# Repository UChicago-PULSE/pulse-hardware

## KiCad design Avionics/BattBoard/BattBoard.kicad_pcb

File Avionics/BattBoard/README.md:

Battery board schematic and board is found here.
Currently have uploaded both the schematic and PCB design

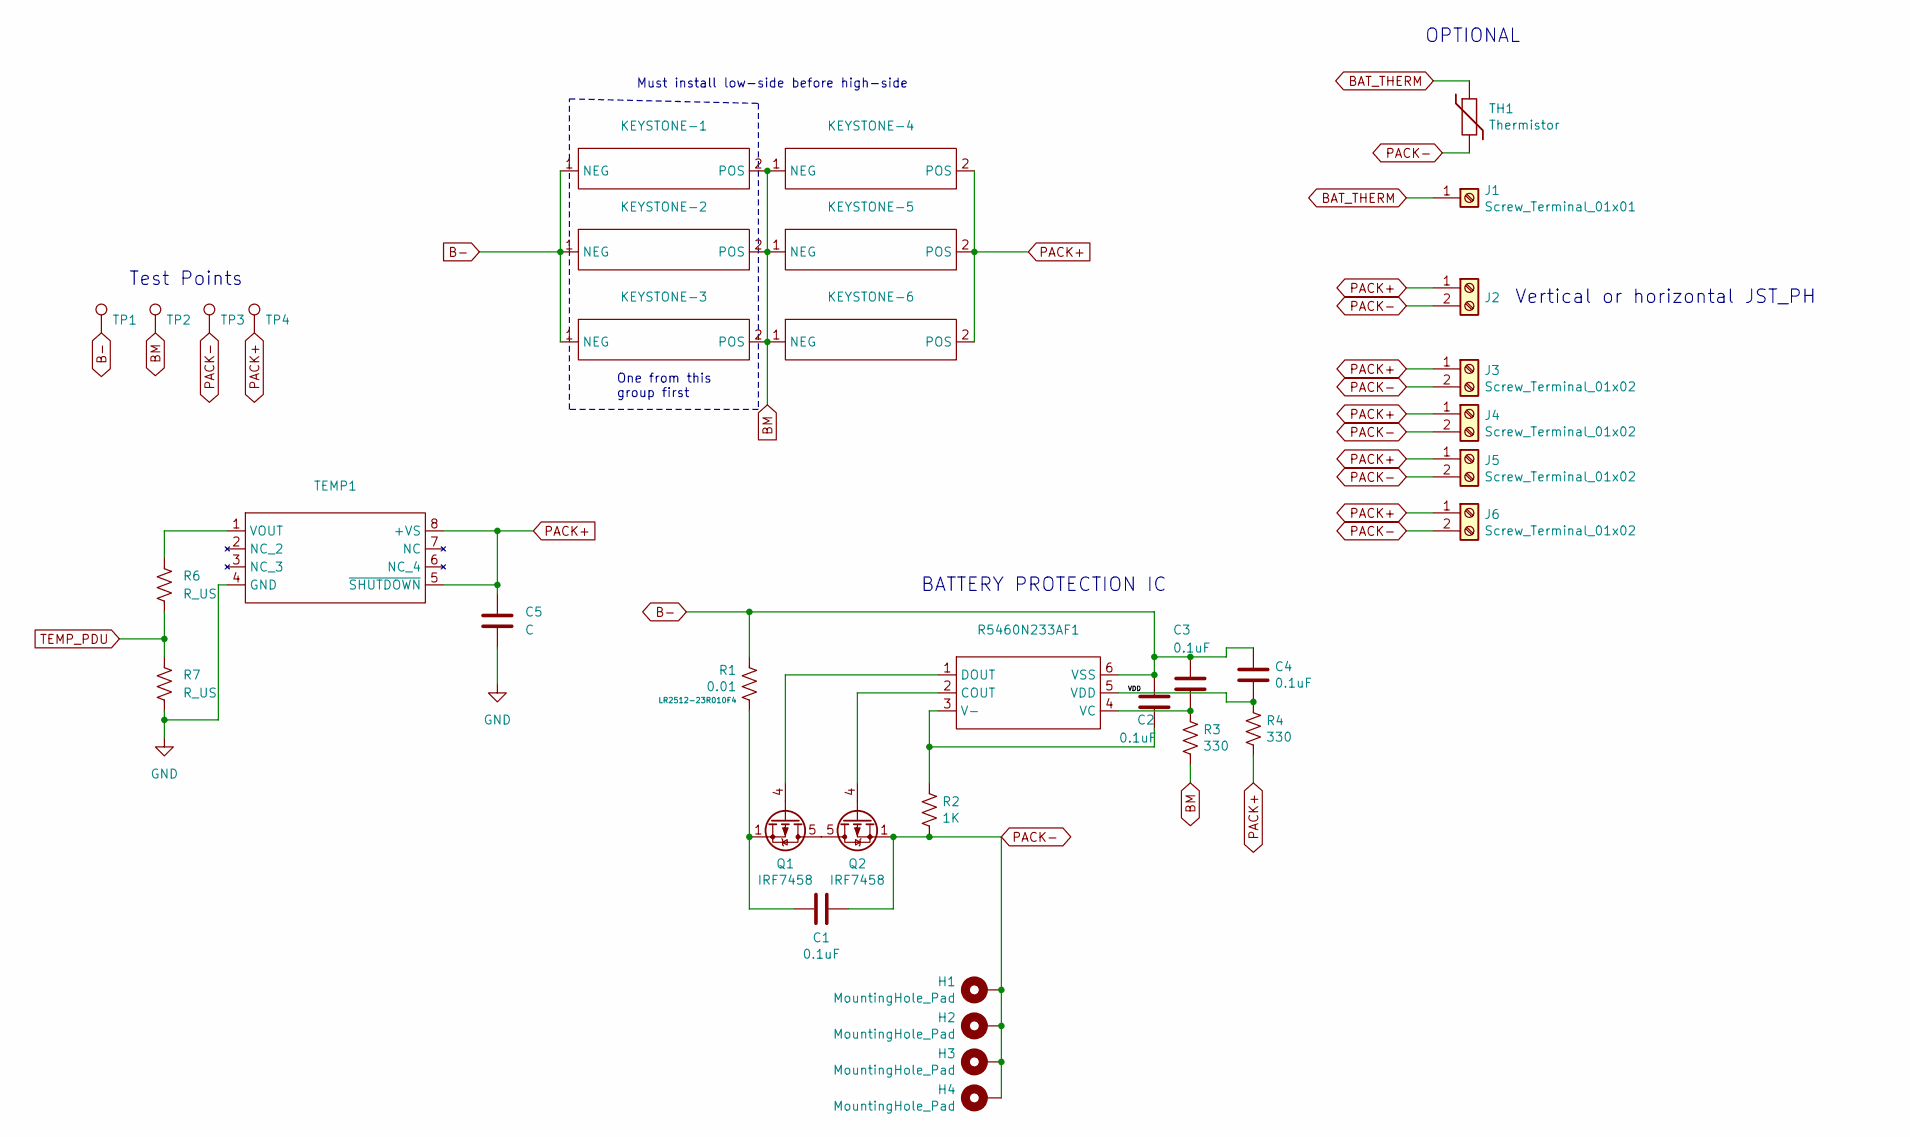
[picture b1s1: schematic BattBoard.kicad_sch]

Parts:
C1, C2, C3, C4: 0.1uF; C_0603_1608Metric
C5: C; C_0603_1608Metric
H1, H2, H3, H4: MountingHole_Pad; MountingHole_3.2mm_M3_DIN965_Pad
J1: Screw_Terminal_01x01; PinHeader_1x01_P1.00mm_Vertical
J2: JST_PH_S2B-PH-SM4; JST_PH_S2B-PH-SM4-TB_1x02-1MP_P2.00mm_Horizontal
J3, J4, J5, J6: Screw_Terminal_01x02; TerminalBlock_Altech_AK300-2_P5.00mm
KEYSTONE-1, KEYSTONE-2, KEYSTONE-3, KEYSTONE-4, KEYSTONE-5, KEYSTONE-6: BatteryHolder_Keystone_1042_1x18650
Q1, Q2: IRF7458; SOIC-8_3.9x4.9mm_P1.27mm
R1: 0.01; R_2512_6332Metric
R2: 1K; R_0603_1608Metric
R3, R4: 330; R_0603_1608Metric
R6, R7: R_US; R_0603_1608Metric
R5460N233AF1: PinHeader_2x03_P2.54mm_Vertical_SMD
TEMP1: Rohm_RPR-0521RS
TH1: Thermistor; R_Axial_DIN0204_L3.6mm_D1.6mm_P5.08mm_Vertical
TP1, TP2, TP3, TP4: TestPoint; TestPoint_Loop_D1.80mm_Drill1.0mm_Beaded

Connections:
/VDD: C4.2, R4.2, R5460N233AF1.5 (VDD)
B-: C2.1, C3.1, C4.1, KEYSTONE-1.1 (NEG), KEYSTONE-2.1 (NEG), KEYSTONE-3.1 (NEG), R1.1, R5460N233AF1.6 (VSS), TP1.1
BAT_THERM: J1.1, TH1.1
BM: KEYSTONE-1.2 (POS), KEYSTONE-2.2 (POS), KEYSTONE-3.2 (POS), KEYSTONE-4.1 (NEG), KEYSTONE-5.1 (NEG), KEYSTONE-6.1 (NEG), R3.1, TP2.1
GND: C5.2, R7.2, TEMP1.4 (GND)
unnamed: C1.1, Q1.1 (S), Q1.2 (S), Q1.3 (S), R1.2
unnamed: Q1.5 (D), Q1.6 (D), Q1.7 (D), Q1.8 (D), Q2.5 (D), Q2.6 (D), Q2.7 (D), Q2.8 (D)
unnamed: Q1.4 (G), R5460N233AF1.1 (DOUT)
unnamed: Q2.4 (G), R5460N233AF1.2 (COUT)
unnamed: C2.2, R2.1, R5460N233AF1.3 (V-)
unnamed: C3.2, R3.2, R5460N233AF1.4 (VC)
unnamed: R6.1, TEMP1.1 (VOUT)
PACK+: C5.1, J2.1, J3.1, J4.1, J5.1, J6.1, KEYSTONE-4.2 (POS), KEYSTONE-5.2 (POS), KEYSTONE-6.2 (POS), R4.1, TEMP1.5 (~SHUTDOWN), TEMP1.8 (+VS), TP4.1
PACK-: C1.2, H1.1, H2.1, H3.1, H4.1, J2.2, J3.2, J4.2, J5.2, J6.2, Q2.1 (S), Q2.2 (S), Q2.3 (S), R2.2, TH1.2, TP3.1
TEMP_PDU: R6.2, R7.1

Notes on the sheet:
Vertical or horizontal JST_PH
Test Points
OPTIONAL
One from this group first
Must install low-side before high-side
BATTERY PROTECTION IC

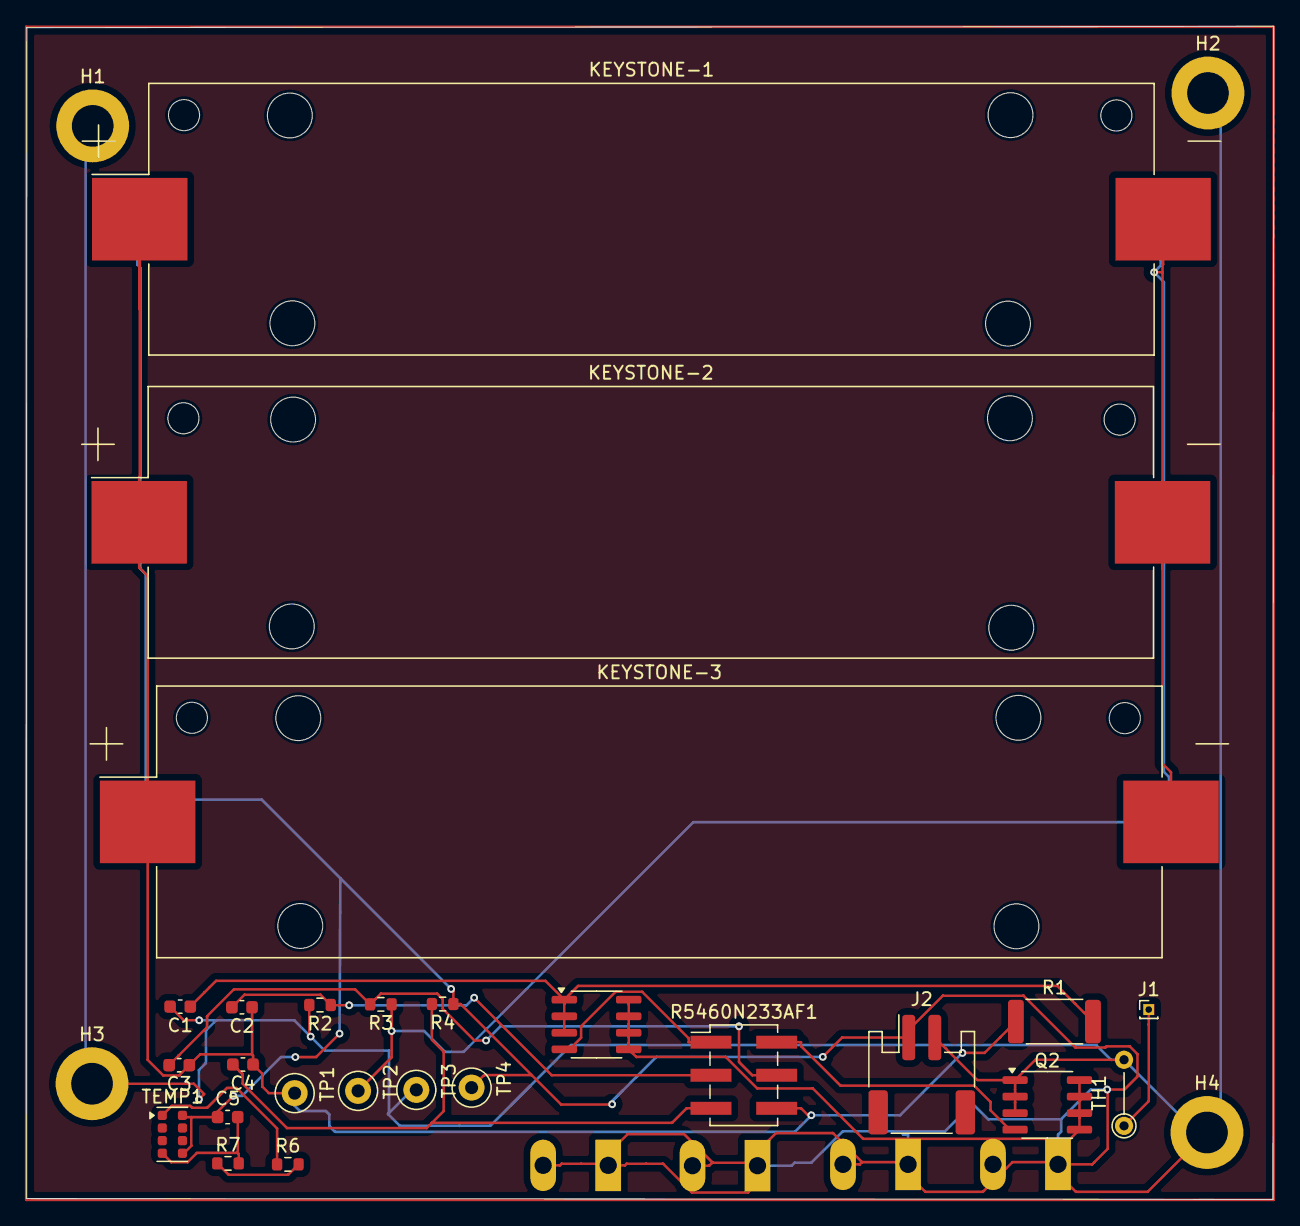
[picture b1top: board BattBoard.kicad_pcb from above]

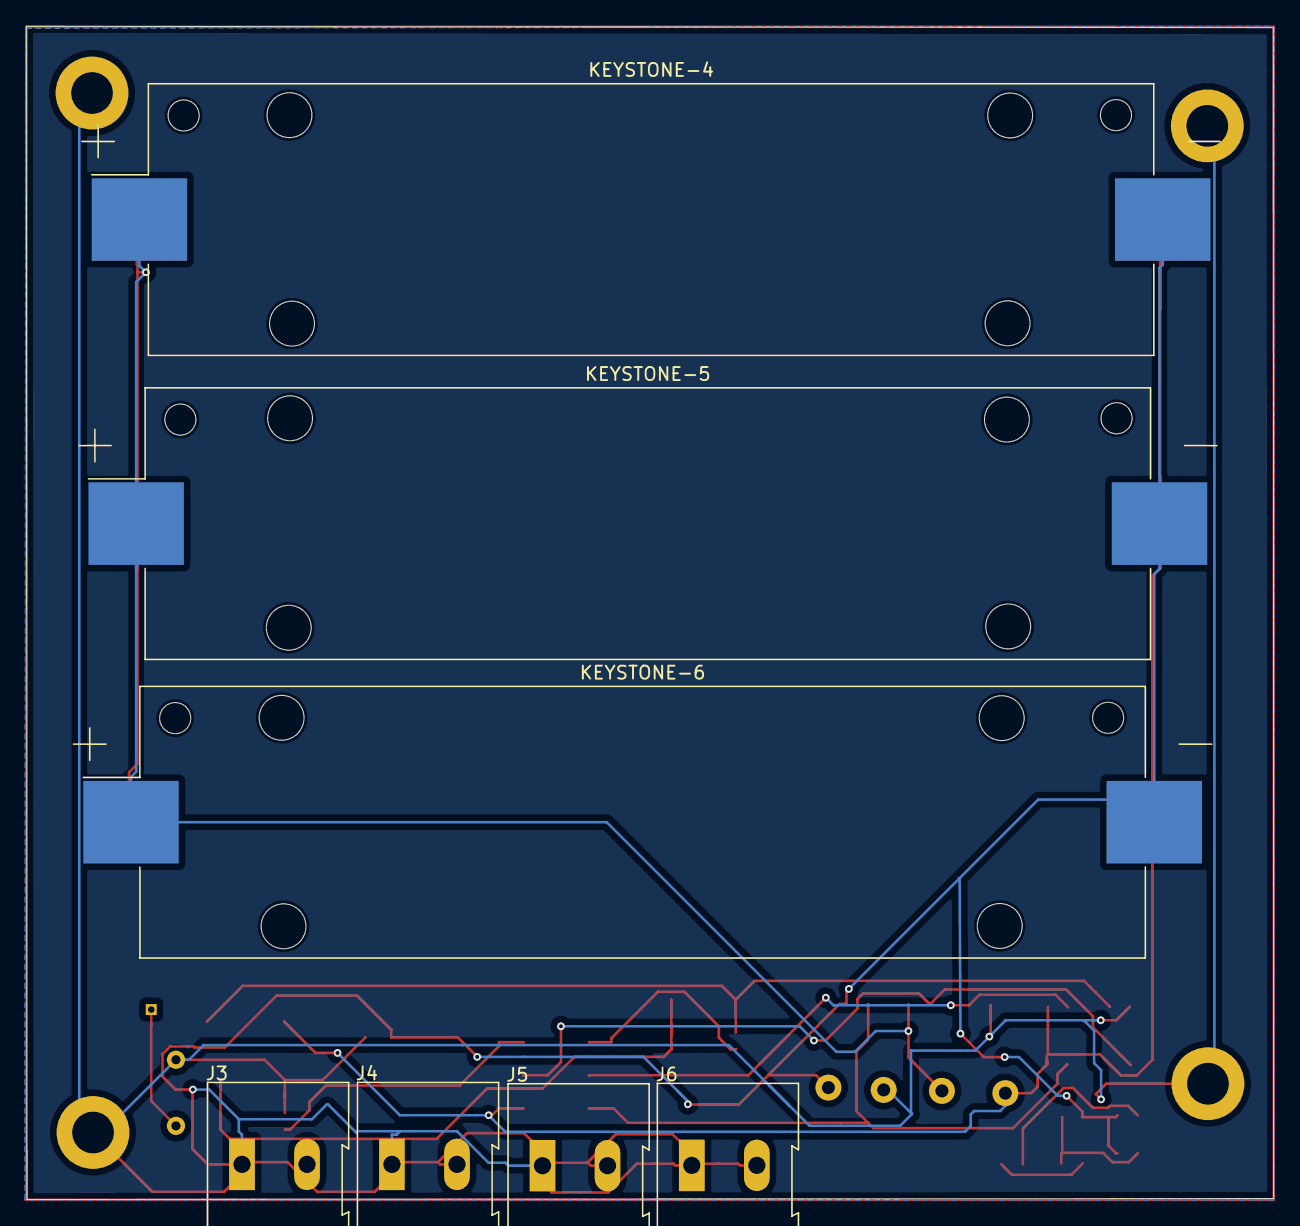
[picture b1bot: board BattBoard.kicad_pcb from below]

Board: 2 copper layers, 95.9 x 90.2 mm, 36 parts (7 on the bottom side), 15 nets.

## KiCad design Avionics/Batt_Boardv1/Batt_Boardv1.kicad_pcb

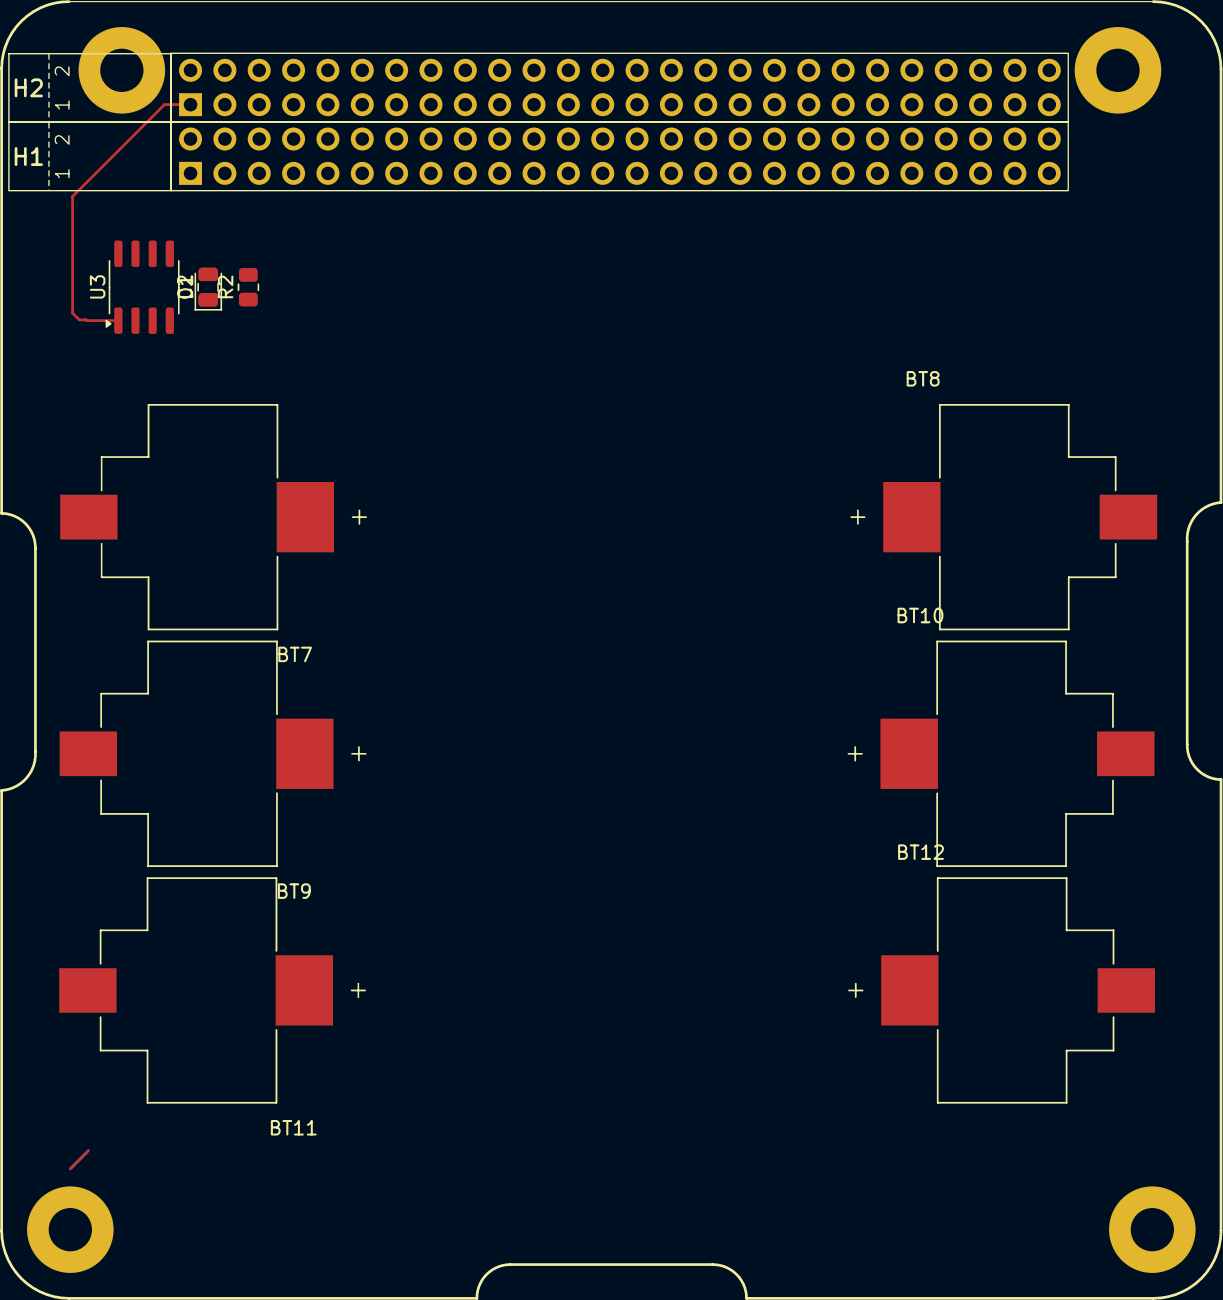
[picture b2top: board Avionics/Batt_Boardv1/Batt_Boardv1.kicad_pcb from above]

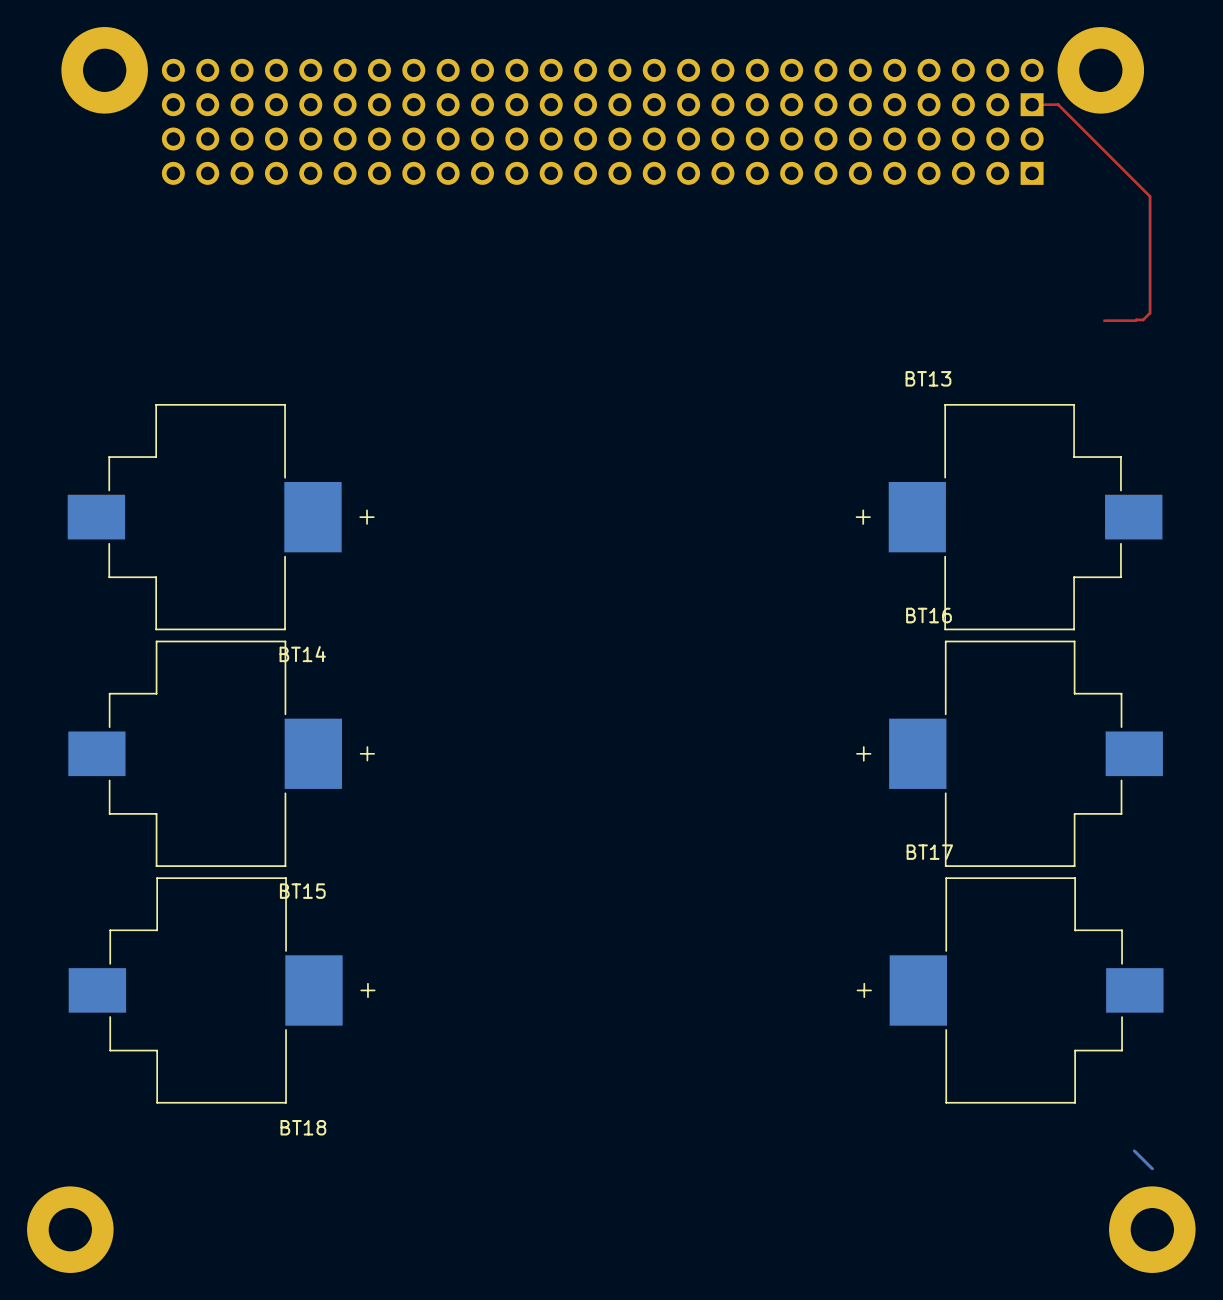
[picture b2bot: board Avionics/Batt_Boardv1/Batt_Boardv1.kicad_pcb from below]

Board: 2 copper layers, 17 parts (6 on the bottom side), 4 nets.

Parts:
BT7, BT8, BT9, BT10, BT11, BT12, BT13, BT14, BT15, BT16, BT17, BT18: 54; BAT_254TR
C2: 0.1µF; C_0805_2012Metric
D1: TEMP_PWR; LED_0805_2012Metric
R2: 15; R_0805_2012Metric
U1: PC104ConnectorFootprint (1)
U3: TMP36xS; SOIC-8_3.9x4.9mm_P1.27mm

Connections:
/batt_board_temp: U1.53 (TEMP_1), U3.1 (V_{OUT})
unnamed: C2.1, D1.2 (A), U3.5 (~SHUTDOWN), U3.8 (+Vs)
unnamed: D1.1 (K), R2.1
unnamed: C2.2, R2.2, U3.4 (GND)

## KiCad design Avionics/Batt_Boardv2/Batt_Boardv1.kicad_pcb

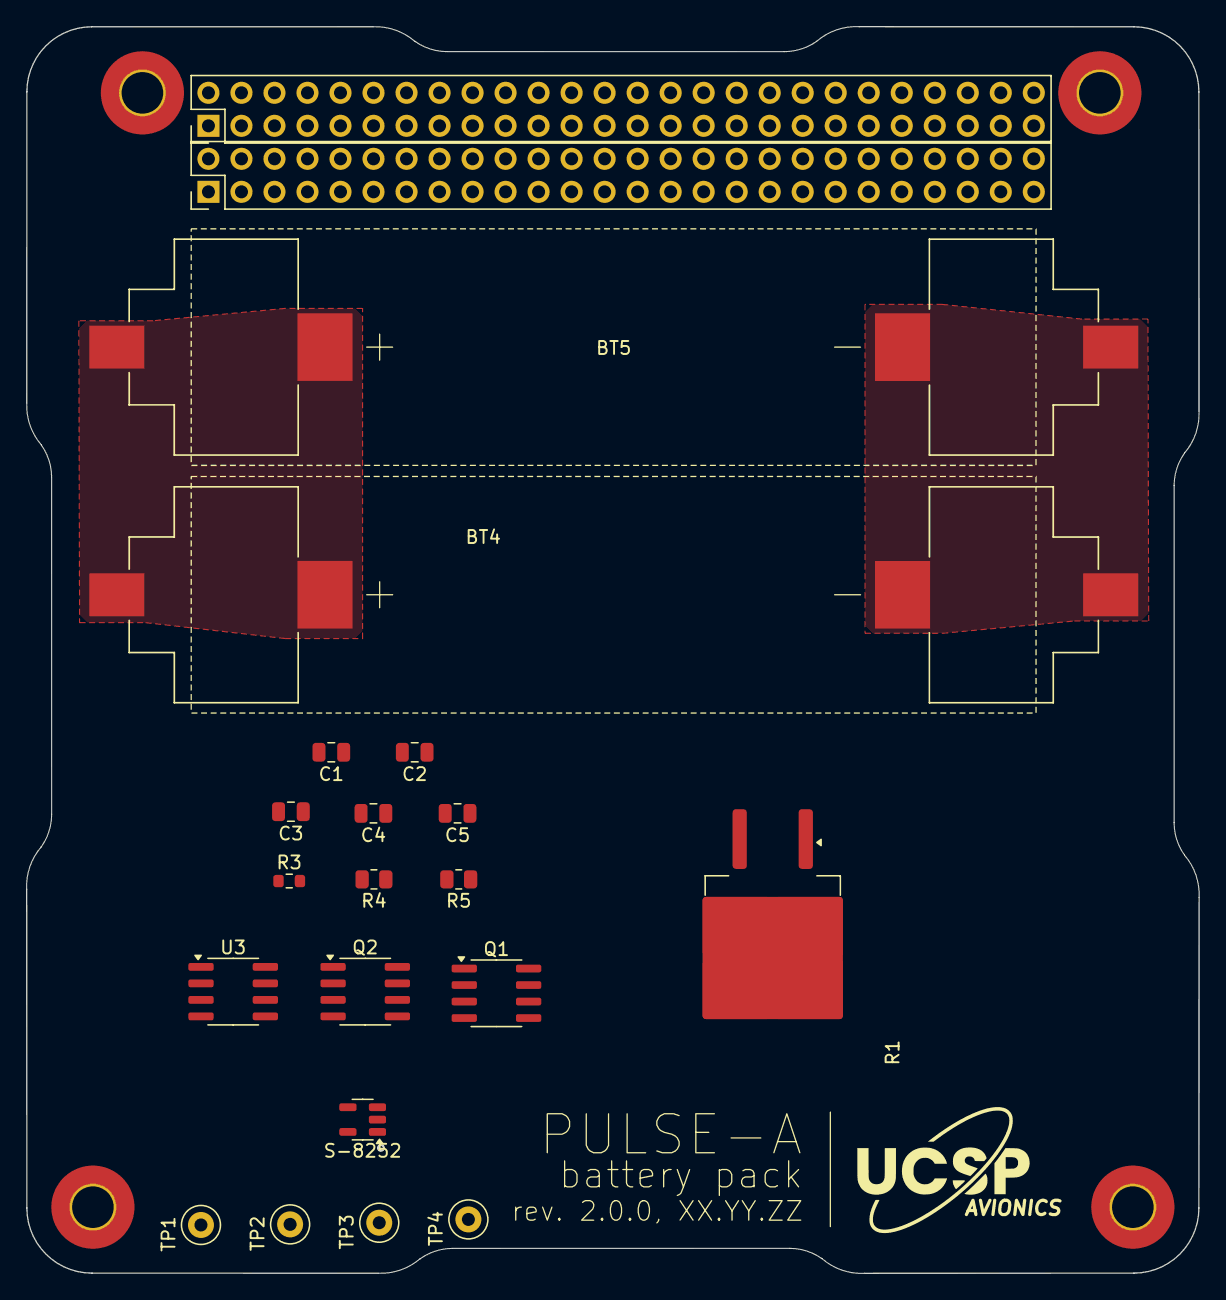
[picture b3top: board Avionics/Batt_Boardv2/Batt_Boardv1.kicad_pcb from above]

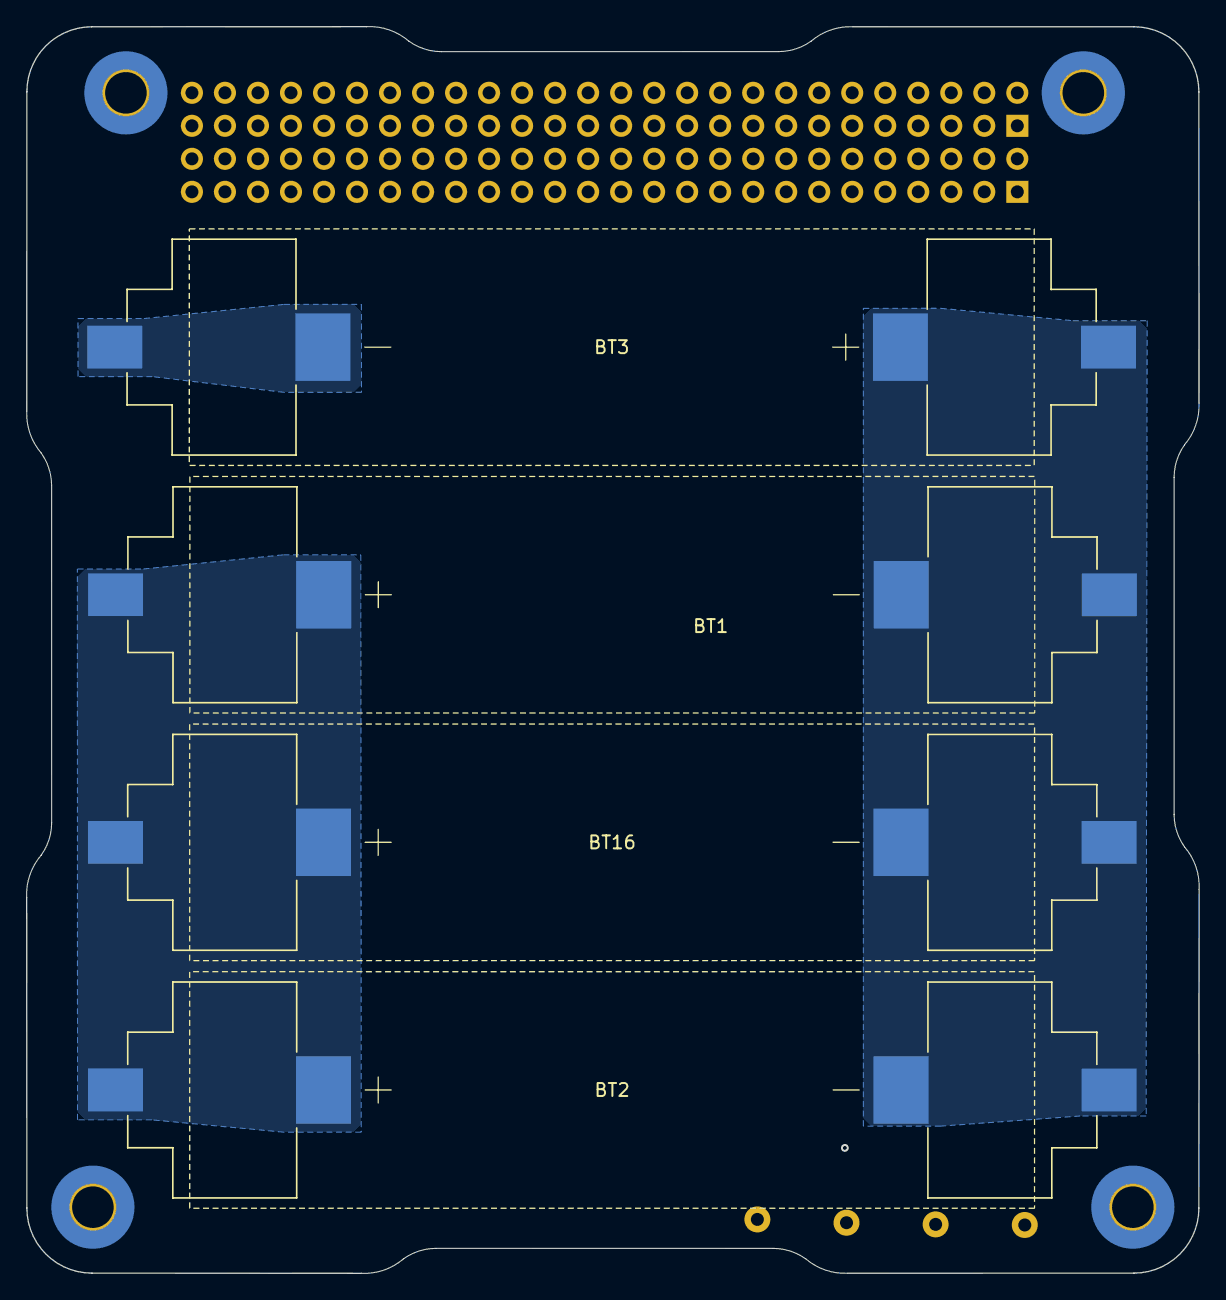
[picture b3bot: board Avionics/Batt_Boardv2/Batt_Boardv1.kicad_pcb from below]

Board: 2 copper layers, 90.2 x 95.9 mm, 29 parts (4 on the bottom side), 16 nets, no tracks yet.

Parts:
BT1, BT2, BT3, BT4, BT5, BT16: 54; BAT_254_1
C1, C3, C4, C5: 0.1uF; C_0805_2012Metric
C2: 0.1µF; C_0805_2012Metric
H1, H2, H3, H4: MountingHole; MountingHole_3.2mm_M3_Pad_TopBottom
J1, J2: Conn_02x26_Odd_Even; PinHeader_2x26_P2.54mm_Vertical
Q1, Q2: IRF7458; SOIC-8_3.9x4.9mm_P1.27mm
R1: 0.01; TO-263-2
R3: 1K; R_0603_1608Metric
R4, R5: 330; R_0805_2012Metric
S-8252: SOT-23-5
TP1, TP2, TP3, TP4: TestPoint; TestPoint_Loop_D1.80mm_Drill1.0mm_Beaded
U3: TMP36xS; SOIC-8_3.9x4.9mm_P1.27mm

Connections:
/3V3: C2.1, U3.5 (~SHUTDOWN), U3.8 (+Vs)
/3V3_BUS: J2.27, J2.28
/5V_BUS: J2.25, J2.26
/B-: BT3.2 (BATT-), BT4.2 (BATT-), BT5.2 (BATT-), C3.1, C4.1, C5.1, R1.1, TP1.1
/BATT_PRE_INH: BT1.1 (BATT+), BT2.1 (BATT+), BT16.1 (BATT+), J1.5, J1.6, J1.7, J1.8, J1.11, J1.12, J1.13, J1.14, R5.1, TP4.1
/BM: BT1.2 (BATT-), BT2.2 (BATT-), BT3.1 (BATT+), BT4.1 (BATT+), BT5.1 (BATT+), BT16.2 (BATT-), R4.1, TP2.1
/EDFA_5V_SW: J2.21, J2.22
/VDD: C5.2, R5.2, S-8252.5 (VDD)
GNDREF: C1.2, C2.2, J1.33, J1.34, J1.35, J1.36, Q2.1 (S), Q2.2 (S), Q2.3 (S), R3.2, TP3.1, U3.4 (GND)
unnamed: C1.1, Q1.1 (S), Q1.2 (S), Q1.3 (S), R1.2
unnamed: Q1.5 (D), Q1.6 (D), Q1.7 (D), Q1.8 (D), Q2.5 (D), Q2.6 (D), Q2.7 (D), Q2.8 (D)
unnamed: Q1.4 (G), S-8252.1 (DOUT)
unnamed: Q2.4 (G), S-8252.2 (COUT)
unnamed: C3.2, R3.1, S-8252.3 (V-)
unnamed: C4.2, R4.2, S-8252.4 (VC)
V_BATT: J2.46, J2.48

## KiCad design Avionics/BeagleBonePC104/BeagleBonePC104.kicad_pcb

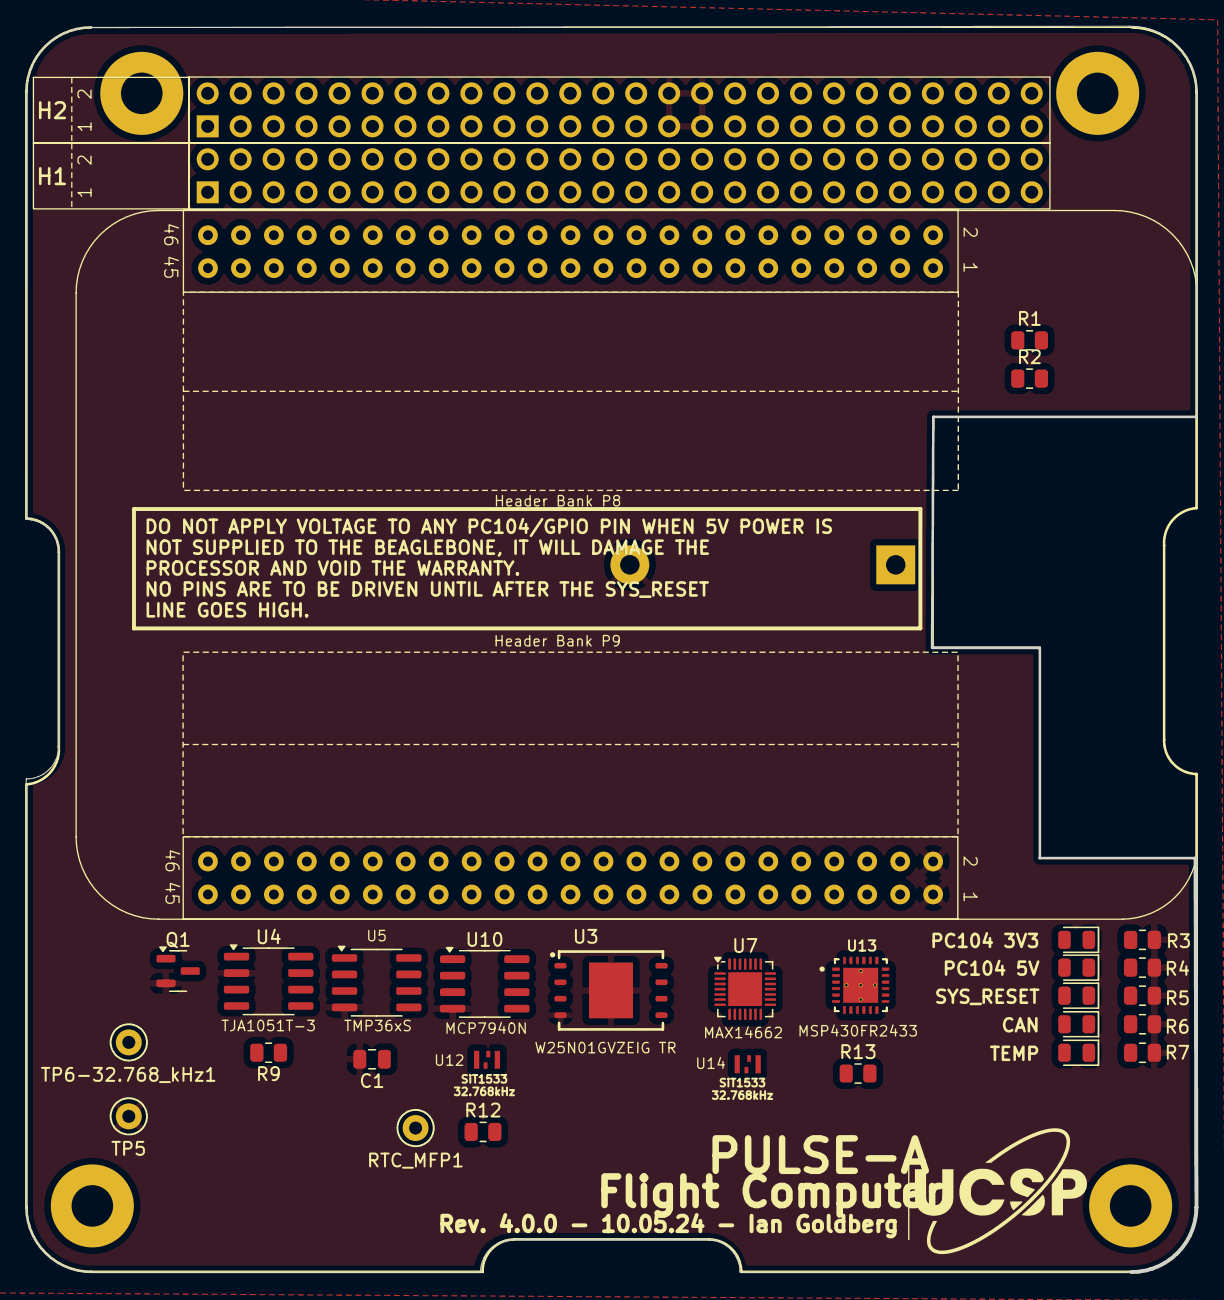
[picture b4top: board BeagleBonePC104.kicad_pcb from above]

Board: 4 copper layers, 90.2 x 96.0 mm, 31 parts (1 on the bottom side), 48 nets, no tracks yet.

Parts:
BT1: Battery_Cell; BatteryHolder_Keystone_106_1x20mm
C1: 0.1µF; C_0805_2012Metric
D1: 3V3 Status; LED_0805_2012Metric
D2: 5V Status; LED_0805_2012Metric
D3: Beaglebone Ready; LED_0805_2012Metric
D4: CAN_PWR; LED_0805_2012Metric
D5: TEMP_PWR; LED_0805_2012Metric
Q1: 2N7002; SOT-23
R1, R2: 2.2k; R_0805_2012Metric
R3, R5, R6, R7: 15; R_0805_2012Metric
R4: 100; R_0805_2012Metric
R9: 120; R_0805_2012Metric
R12, R13: 10k; R_0805_2012Metric
RTC_MFP1: TestPoint; TestPoint_Keystone_5000-5004_Miniature
TP5, TP6-32.768_kHz1: TestPoint; TestPoint_Keystone_5000-5004_Miniature
U1: BeagleBoneBlackFootprint
U2: PC104ConnectorFootprint
U3: W25N01GVZEIG_TR; SON127P800X600X80-9N
U4: TJA1051T-3; SOIC-8_3.9x4.9mm_P1.27mm
U5: TMP36xS; SOIC-8_3.9x4.9mm_P1.27mm
U7: MAX14662; QFN-28-1EP_4x4mm_P0.4mm_EP2.6x2.6mm
U10: MCP7940N-xSN; SOIC-8_3.9x4.9mm_P1.27mm
U12, U14: XTAL4_SiT1533_SIT
U13: QFN50P400X400X100-25N

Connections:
/3V3: D1.2 (A), U2.25 (3V3_MAIN), U2.26 (3V3_MAIN), U2.79 (3V3_MAIN), U2.80 (3V3_MAIN), U3.8 (VCC), U7.2 (A1), U7.3 (A2), U7.4 (A3), U7.5 (A4), U7.6 (A5), U7.7 (A6), U7.8 (A7), U7.9 (A8), U7.26 (V_{CC})
/5V: D2.2 (A), U1.5 (VDD_5V), U1.6 (VDD_5V), U2.77 (5V_MAIN), U2.78 (5V_MAIN)
/CAN1_RX: U1.24 (DCAN1_RX), U4.4 (RXD)
/CAN1_TX: U1.26 (DCAN1_TX), U4.1 (TXD)
/CAN_H: R9.1, U2.3 (CANH1), U4.7 (CANH)
/CAN_L: R9.2, U2.1 (CANL1), U4.6 (CANL)
/CAN_PWR: D4.2 (A), U4.3 (VCC), U4.5 (VIO), U7.18 (B4)
/CAN_SLNT: U1.25 (GPIO3_21), U2.102, U4.8 (S)
/FC_TEMP: U1.40 (AIN1), U5.1 (V_{OUT})
/GPI02_22: U1.27 (GPIO2_22), U2.29
/GPIO0_7: U1.42 (GPIO0_7), U13.9 (P1.2/UCB0SIMO/UCB0SDA/TA0.2/A2/Veref-)
/GPIO1_12: U1.12 (GPIO1_12), U2.13
/GPIO1_13: U1.11 (GPIO1_13), U2.11
/GPIO1_14: U1.16 (GPIO1_14), U2.69
/GPIO1_15: U1.15 (GPIO1_15), U2.17
/GPIO1_26: U1.14 (GPIO0_26), U2.15
/GPIO1_27: U1.17 (GPIO0_27), U2.21
/GPIO2_1: U1.18 (GPIO2_1), U2.23
/GPIO2_8: U1.43 (GPIO2_8), U2.30
/GPIO2_9: U1.44 (GPIO2_9), U2.34
/GPIO2_10: U1.41 (GPIO2_10), U2.24
/GPIO2_12: U1.39 (GPIO2_12), U2.46
/GPIO2_24: U1.28 (GPIO2_24), U2.45
/I2C_SCL: R1.2, U2.43 (I2C1_SCL), U7.24 (SCLK/SCL), U10.6 (SCL)
/I2C_SDA: R2.1, U2.41 (I2C1_SDA), U7.27 (DIN/SDA), U10.5 (SDA)
/MSP430_PWR: R13.1, U7.21 (B1), U13.24 (DVCC), U14.4 (Vdd)
/MSP430_RST: Q1.1 (G), U1.45 (GPIO2_6)
/NAND_~HOLD(I/O3): U1.30 (GPIO2_25), U3.7 (/HOLD(IO3))
/NAND_~WP(I/O2): U1.29 (GPIO2_23), U3.3 (/WP(IO2))
/RTC_MFP: R12.2, RTC_MFP1.1, U10.7 (MFP)
/RTC_PWR: R12.1, U7.20 (B2), U10.8 (VCC), U12.4 (Vdd)
/SPI_SCLK: U1.31 (SPI1_SCLK), U3.6 (CLK)
/SPWTCK: U2.52, U13.2 (TEST/SBWTCK)
/SPWTDIO: Q1.3 (D), R13.2, U2.51, U13.1 (RST/NMI/SBWTDIO)
/SYS_RESETn: U1.10 (SYS_RESETn), U2.12 (BGLBON_RST), U13.7 (P1.0/UCB0STE/TA0CLK/A0/Veref+)
/TEMP_PWR: C1.1, D5.2 (A), U5.5 (~SHUTDOWN), U5.8 (+Vs), U7.19 (B3)
/UART_RX: U1.22 (UART2_RXD), U2.20 (UART_1_RX), U2.35 (GNSS_UART_RX), U13.3 (P1.4/UCA0TXD/UCA0SIMO/TA1.2/TCK/A4/VREF+), U13.4 (P1.5/UCA0RXD/UCA0SOMI/TA1.1/TMS/A5)
/UART_TX: U1.21 (UART2_TXD), U2.19 (UART_1_TX), U2.33 (GNSS_UART_TX)
GND: BT1.2 (-), C1.2, Q1.2 (S), R3.2, R4.2, R5.2, R6.2, R7.2, TP5.1, U1.1 (GND), U1.2 (GND), U2.81 (GND), U2.82 (GND), U2.83 (GND), U2.84 (GND), U3.4 (GND), U3.9 (GND), U4.2 (GND), U5.4 (GND), U7.11 (GND), U7.25 (GND), U7.29 (GND), U10.4 (VSS), U12.2 (GND), U13.18 (DVSS), U13.21 (DVSS), U14.2 (GND)
unnamed: BT1.1 (+), U10.3 (VBAT)
unnamed: D1.1 (K), R3.1
unnamed: D2.1 (K), R4.1
unnamed: D3.1 (K), R5.1
unnamed: D4.1 (K), R6.1
unnamed: D5.1 (K), R7.1
unnamed: R1.1, R2.2, U1.4 (DC_3.3V)
unnamed: TP6-32.768_kHz1.1, U10.1 (X1), U12.3 (CLK_OUT)
unnamed: U13.22 (P2.1/XIN), U14.3 (CLK_OUT)

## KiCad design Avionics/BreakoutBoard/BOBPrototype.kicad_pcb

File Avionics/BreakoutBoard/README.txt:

Breakout Board Files and other contents found here.
Currently: Schematic, BOB footprint, and base BOB board has been uploaded

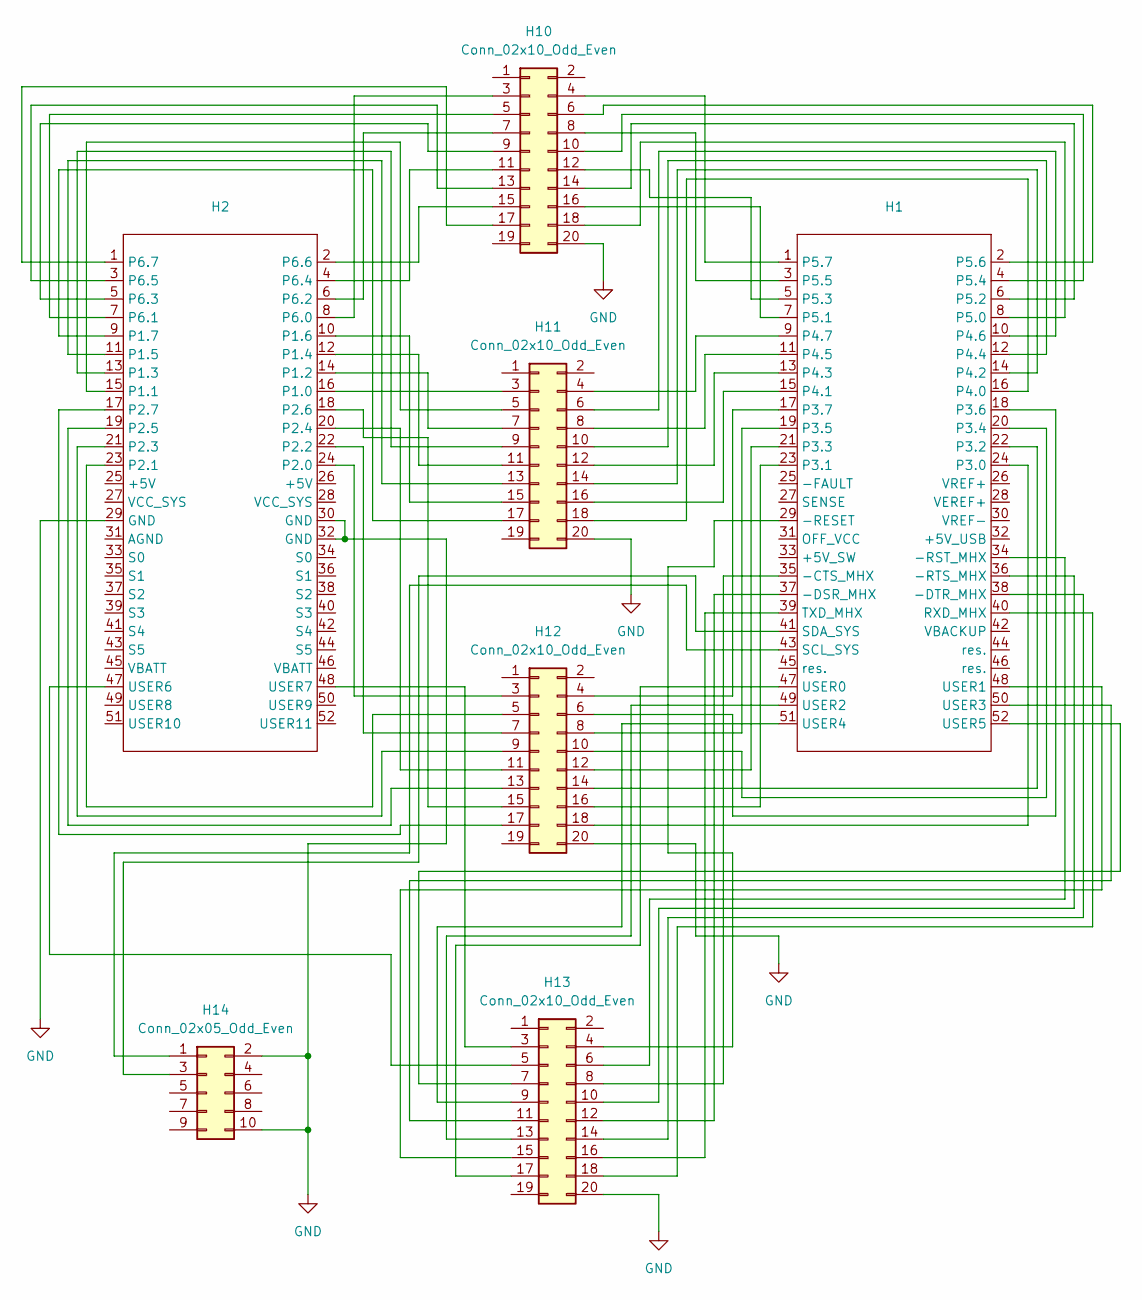
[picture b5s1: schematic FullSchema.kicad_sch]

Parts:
H1, H2: PinSocket_2x26_P1.27mm_Vertical
H10, H11, H12, H13: Conn_02x10_Odd_Even; PinHeader_2x10_P2.00mm_Vertical
H14: Conn_02x05_Odd_Even; PinHeader_2x05_P2.00mm_Vertical

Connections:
GND: H2.29 (GND), H2.30 (GND), H2.32 (GND), H10.20, H11.20, H12.20, H13.20, H14.2, H14.10; also elsewhere on the board
unnamed: H1.35 (-CTS_MHX), H13.8
unnamed: H1.37 (-DSR_MHX), H13.12
unnamed: H1.38 (-DTR_MHX), H13.14
unnamed: H1.29 (-RESET), H13.4
unnamed: H1.34 (-RST_MHX), H13.6
unnamed: H1.36 (-RTS_MHX), H13.10
unnamed: H1.24 (P3.0), H12.18
unnamed: H1.23 (P3.1), H12.16
unnamed: H1.22 (P3.2), H12.14
unnamed: H1.21 (P3.3), H12.12
unnamed: H1.20 (P3.4), H12.10
unnamed: H1.19 (P3.5), H12.8
unnamed: H1.18 (P3.6), H12.6
unnamed: H1.17 (P3.7), H12.4
unnamed: H1.16 (P4.0), H11.18
unnamed: H1.15 (P4.1), H11.16
unnamed: H1.14 (P4.2), H11.14
unnamed: H1.13 (P4.3), H11.12
unnamed: H1.12 (P4.4), H11.10
unnamed: H1.11 (P4.5), H11.8
unnamed: H1.10 (P4.6), H11.6
unnamed: H1.9 (P4.7), H11.4
unnamed: H1.8 (P5.0), H10.18
unnamed: H1.7 (P5.1), H10.16
unnamed: H1.6 (P5.2), H10.14
unnamed: H1.5 (P5.3), H10.12
unnamed: H1.4 (P5.4), H10.10
unnamed: H1.3 (P5.5), H10.8
unnamed: H1.2 (P5.6), H10.6
unnamed: H1.1 (P5.7), H10.4
unnamed: H1.40 (RXD_MHX), H13.18
unnamed: H1.43 (SCL_SYS), H14.1
unnamed: H1.41 (SDA_SYS), H14.3
unnamed: H1.39 (TXD_MHX), H13.16
unnamed: H1.47 (USER0), H13.17
unnamed: H1.48 (USER1), H13.15
unnamed: H1.49 (USER2), H13.13
unnamed: H1.50 (USER3), H13.11
unnamed: H1.51 (USER4), H13.9
unnamed: H1.52 (USER5), H13.7
unnamed: H2.8 (P6.0), H10.3
unnamed: H2.7 (P6.1), H10.5
unnamed: H2.6 (P6.2), H10.7
unnamed: H2.5 (P6.3), H10.9
unnamed: H2.4 (P6.4), H10.11
unnamed: H2.3 (P6.5), H10.13
unnamed: H2.2 (P6.6), H10.15
unnamed: H2.1 (P6.7), H10.17
unnamed: H2.16 (P1.0), H11.3
unnamed: H2.15 (P1.1), H11.5
unnamed: H2.14 (P1.2), H11.7
unnamed: H2.13 (P1.3), H11.9
unnamed: H2.12 (P1.4), H11.11
unnamed: H2.11 (P1.5), H11.13
unnamed: H2.10 (P1.6), H11.15
unnamed: H2.9 (P1.7), H11.17
unnamed: H2.24 (P2.0), H12.3
unnamed: H2.23 (P2.1), H12.5
unnamed: H2.22 (P2.2), H12.7
unnamed: H2.21 (P2.3), H12.9
unnamed: H2.20 (P2.4), H12.11
unnamed: H2.19 (P2.5), H12.13
unnamed: H2.18 (P2.6), H12.15
unnamed: H2.17 (P2.7), H12.17
unnamed: H2.48 (USER7), H13.3
unnamed: H2.47 (USER6), H13.5

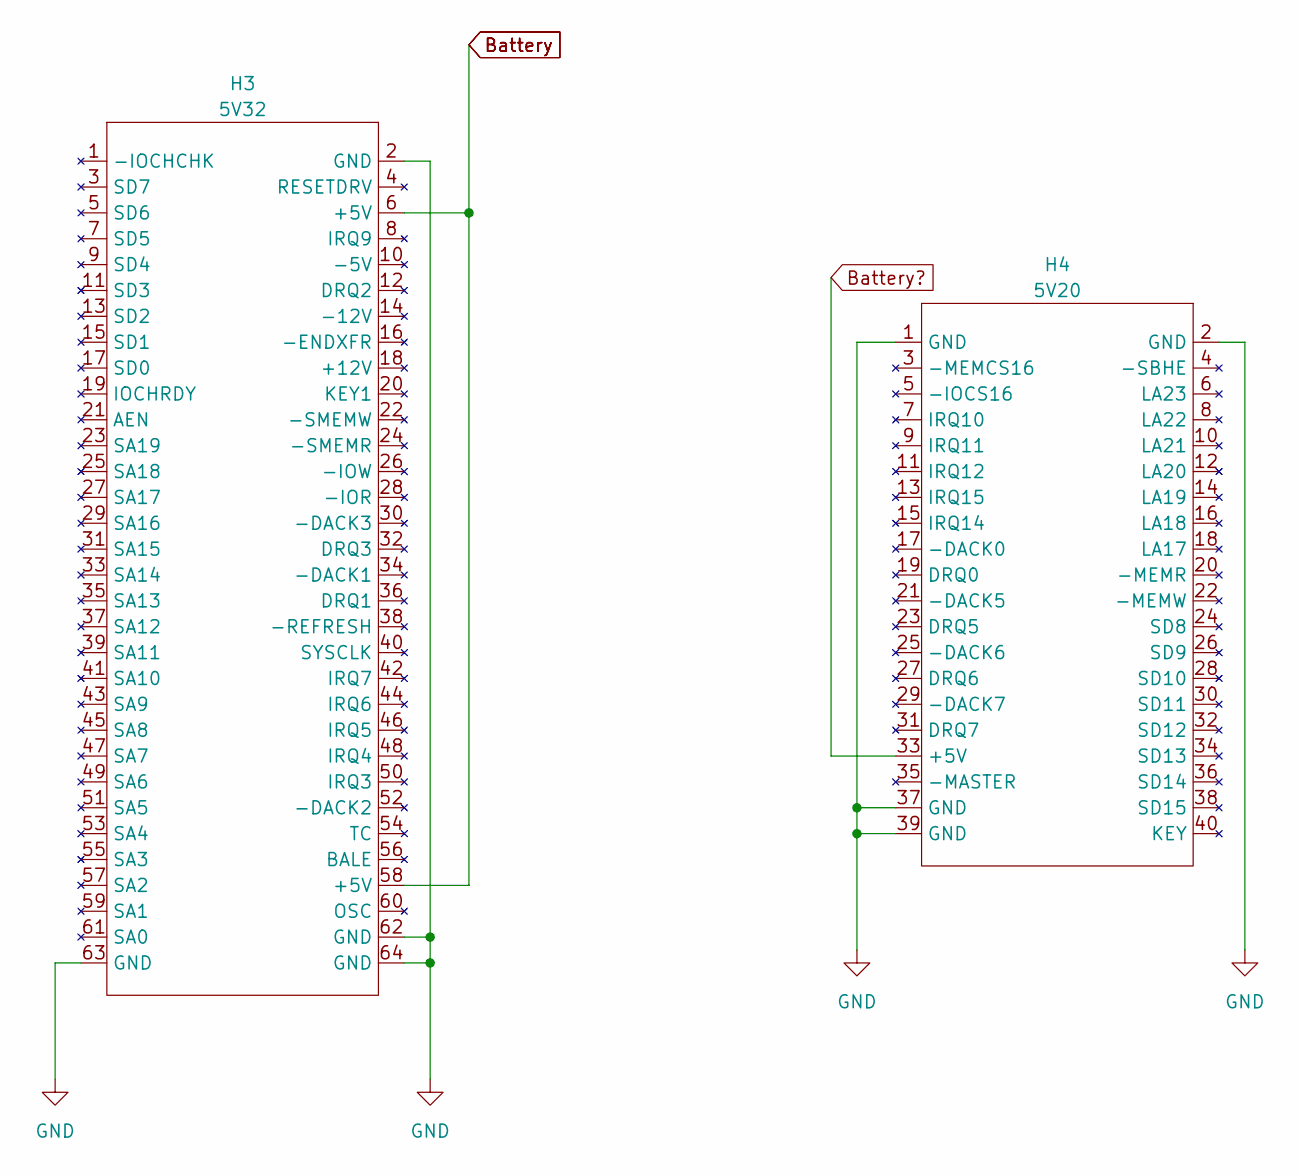
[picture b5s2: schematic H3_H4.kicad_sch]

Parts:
H3: 5V32; H3
H4: 5V20; H4

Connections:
Battery: H3.6 (+5V), H3.58 (+5V)
Battery?: H4.33 (+5V)
GND: H3.2 (GND), H3.62 (GND), H3.63 (GND), H3.64 (GND), H4.1 (GND), H4.2 (GND), H4.37 (GND), H4.39 (GND); also elsewhere on the board
